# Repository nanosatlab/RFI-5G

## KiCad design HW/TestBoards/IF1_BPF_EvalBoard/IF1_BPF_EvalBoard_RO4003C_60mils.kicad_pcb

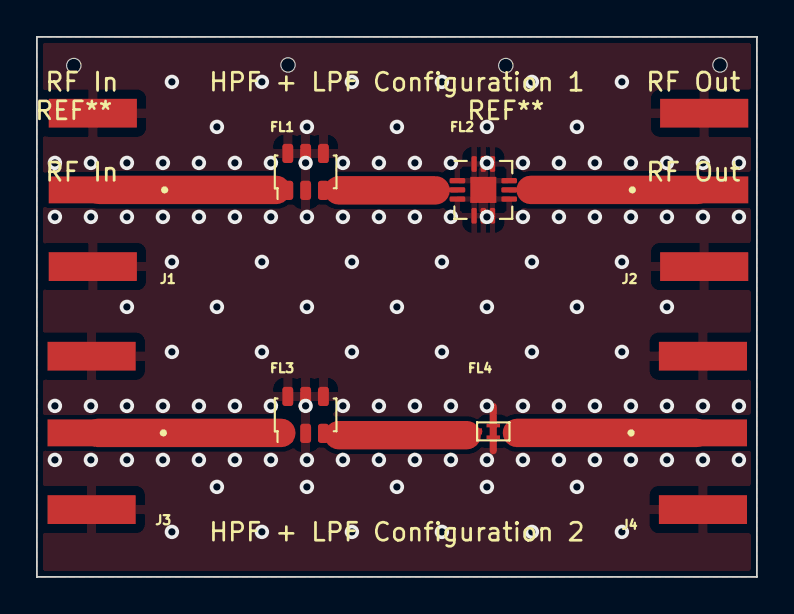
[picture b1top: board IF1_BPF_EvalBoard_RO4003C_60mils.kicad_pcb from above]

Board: 2 copper layers, 40.0 x 30.0 mm, 8 parts (0 on the bottom side), 7 nets.

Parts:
FL1, FL3: HFCN-5500; Filter_Mini-Circuits_FV1206-1
FL2: XLF-962+; QFN-12-1EP_3x3mm_P0.51mm_EP1.45x1.45mm
FL4: LFCW-8000+; JC0603C-1
J1, J2, J3, J4: SMA; LINX_CONSMA020.062-G

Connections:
/HPF_out1: FL1.3 (OUT), FL2.2 (In)
/HPF_out2: FL3.3 (OUT), FL4.1 (In)
/RF_In1: FL1.1 (IN), J1.1 (RF)
/RF_In2: FL3.1 (IN), J3.1 (RF)
/RF_Out1: FL2.8 (Out), J2.1 (RF)
/RF_Out2: FL4.3 (Out), J4.1 (RF)
GND: FL1.2 (GND), FL1.4 (GND), FL1.5 (GND), FL1.6 (GND), FL2.1 (GND), FL2.3 (GND), FL2.4 (NC), FL2.5 (NC), FL2.6 (NC), FL2.7 (GND), FL2.9 (GND), FL2.10 (NC), FL2.11 (NC), FL2.12 (NC), FL2.13 (NC), FL3.2 (GND), FL3.4 (GND), FL3.5 (GND), FL3.6 (GND), FL4.2 (GND), FL4.4 (GND), J1.S1, J1.S2, J1.S3, J1.S4, J2.S1, J2.S2, J2.S3, J2.S4, J3.S1, J3.S2, J3.S3, J3.S4, J4.S1, J4.S2, J4.S3, J4.S4

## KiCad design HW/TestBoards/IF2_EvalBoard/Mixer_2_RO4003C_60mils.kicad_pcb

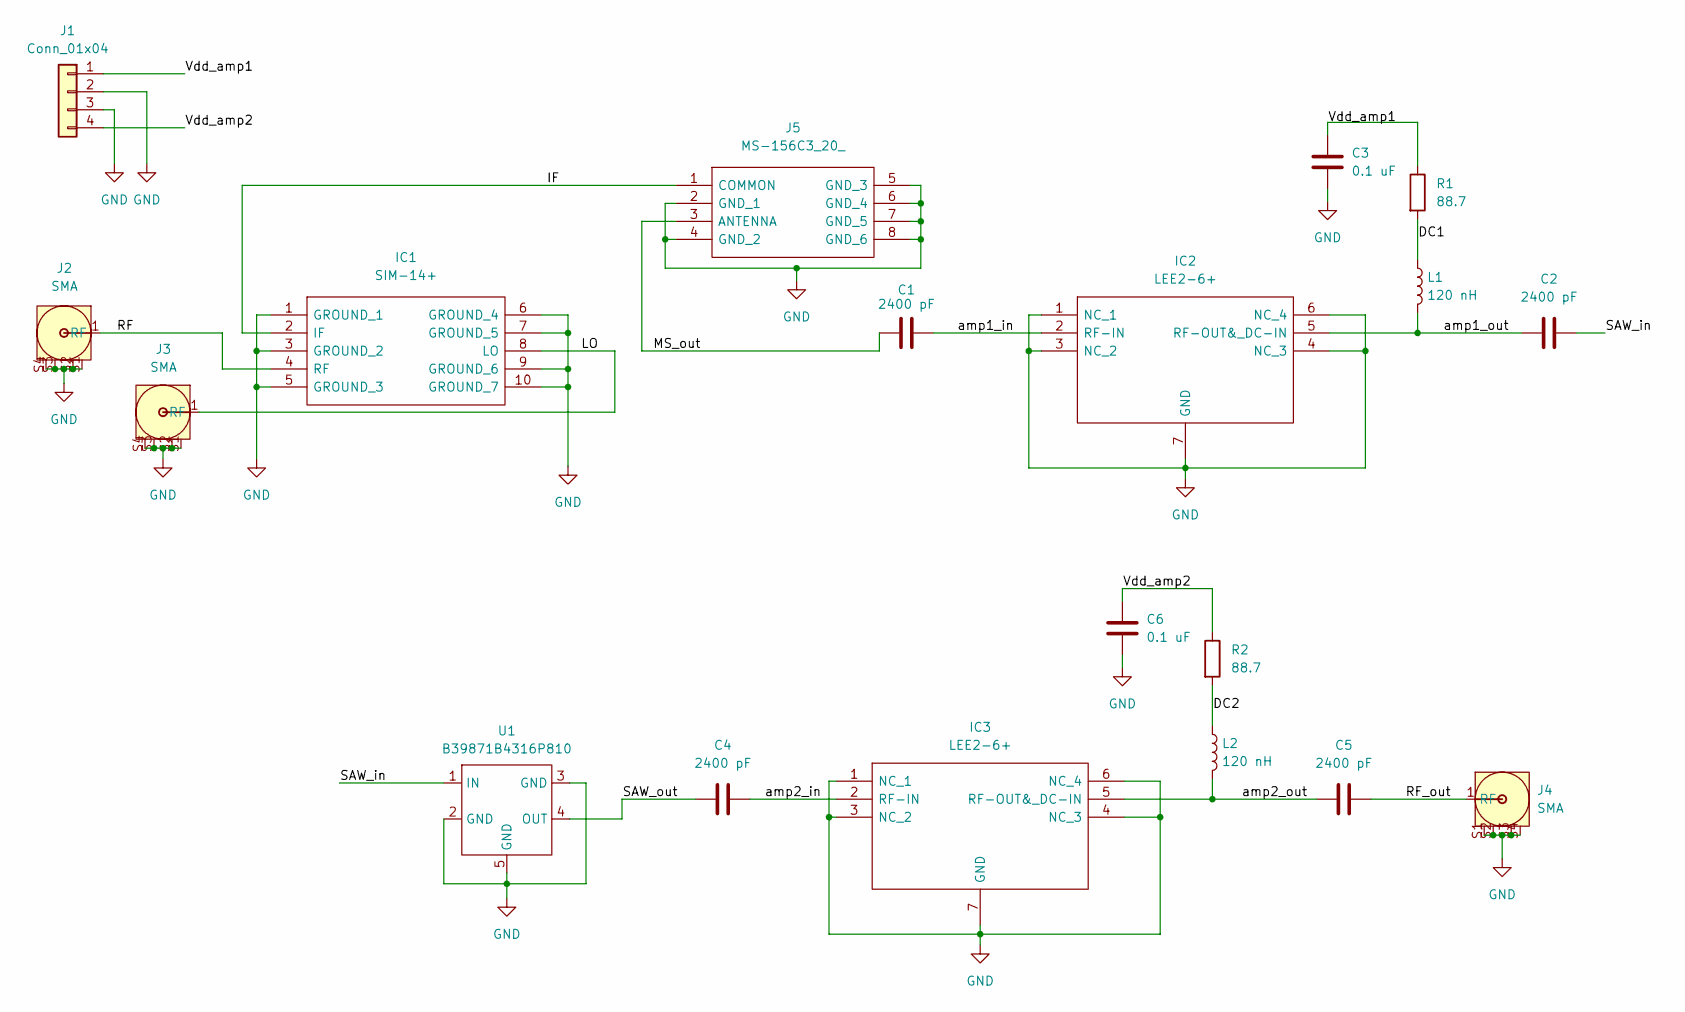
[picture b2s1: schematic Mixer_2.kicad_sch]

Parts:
C1, C2, C4, C5: 2400 pF; C_0603_1608Metric_Pad1.08x0.95mm_HandSolder
C3, C6: 0.1 uF; C_0603_1608Metric_Pad1.08x0.95mm_HandSolder
IC1: SIM-14+; SIM14; Manufacturer_Part_Number SIM-14+
IC2, IC3: LEE2-6+; SON65P200X200X105-7N; Mouser Part Number 139-LEE2-6
J1: Conn_01x04; PinHeader_1x04_P1.27mm_Vertical
J2, J3, J4: SMA; LINX_CONSMA020.062-G
J5: MS-156C3_20_; MS156C320; Mouser Part Number 798-MS-156C320
L1, L2: 120 nH; L_0402_1005Metric_Pad0.77x0.64mm_HandSolder
R1, R2: 88.7; R_0402_1005Metric_Pad0.72x0.64mm_HandSolder
U1: B39871B4316P810

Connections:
/DC1: L1.1, R1.2
/DC2: L2.1, R2.2
/IF: IC1.2 (IF), J5.1 (COMMON)
/LO: IC1.8 (LO), J3.1 (RF)
/MS_out: C1.1, J5.3 (ANTENNA)
/RF: IC1.4 (RF), J2.1 (RF)
/RF_out: C5.2, J4.1 (RF)
/SAW_in: C2.2, U1.1 (IN)
/SAW_out: C4.1, U1.4 (OUT)
/Vdd_amp1: C3.2, J1.1, R1.1
/Vdd_amp2: C6.2, J1.4, R2.1
/amp1_in: C1.2, IC2.2 (RF-IN)
/amp1_out: C2.1, IC2.5 (RF-OUT&_DC-IN), L1.2
/amp2_in: C4.2, IC3.2 (RF-IN)
/amp2_out: C5.1, IC3.5 (RF-OUT&_DC-IN), L2.2
GND: C3.1, C6.1, IC1.1 (GROUND_1), IC1.3 (GROUND_2), IC1.5 (GROUND_3), IC1.6 (GROUND_4), IC1.7 (GROUND_5), IC1.9 (GROUND_6), IC1.10 (GROUND_7), IC2.1 (NC_1), IC2.3 (NC_2), IC2.4 (NC_3), IC2.6 (NC_4), IC2.7 (GND), IC3.1 (NC_1), IC3.3 (NC_2), IC3.4 (NC_3), IC3.6 (NC_4), IC3.7 (GND), J1.2, J1.3, J2.S1, J2.S2, J2.S3, J2.S4, J3.S1, J3.S2, J3.S3, J3.S4, J4.S1, J4.S2, J4.S3, J4.S4, J5.2 (GND_1), J5.4 (GND_2), J5.5 (GND_3), J5.6 (GND_4), J5.7 (GND_5), J5.8 (GND_6), U1.2 (GND), U1.3 (GND), U1.5 (GND)

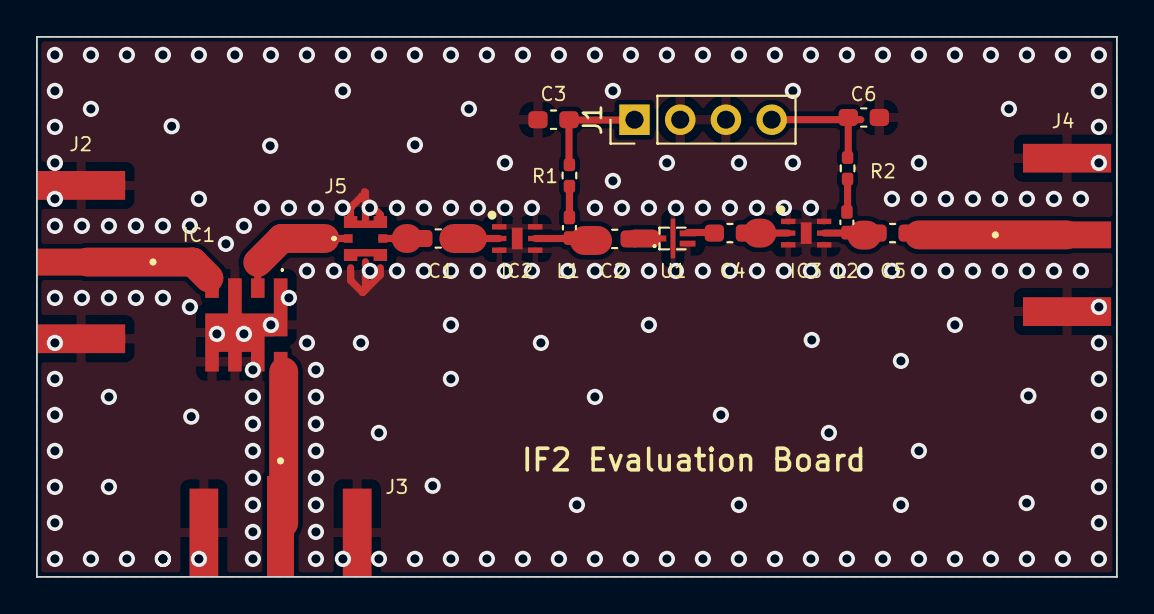
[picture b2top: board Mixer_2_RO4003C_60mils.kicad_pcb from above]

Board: 2 copper layers, 60.0 x 30.0 mm, 19 parts (0 on the bottom side), 16 nets.

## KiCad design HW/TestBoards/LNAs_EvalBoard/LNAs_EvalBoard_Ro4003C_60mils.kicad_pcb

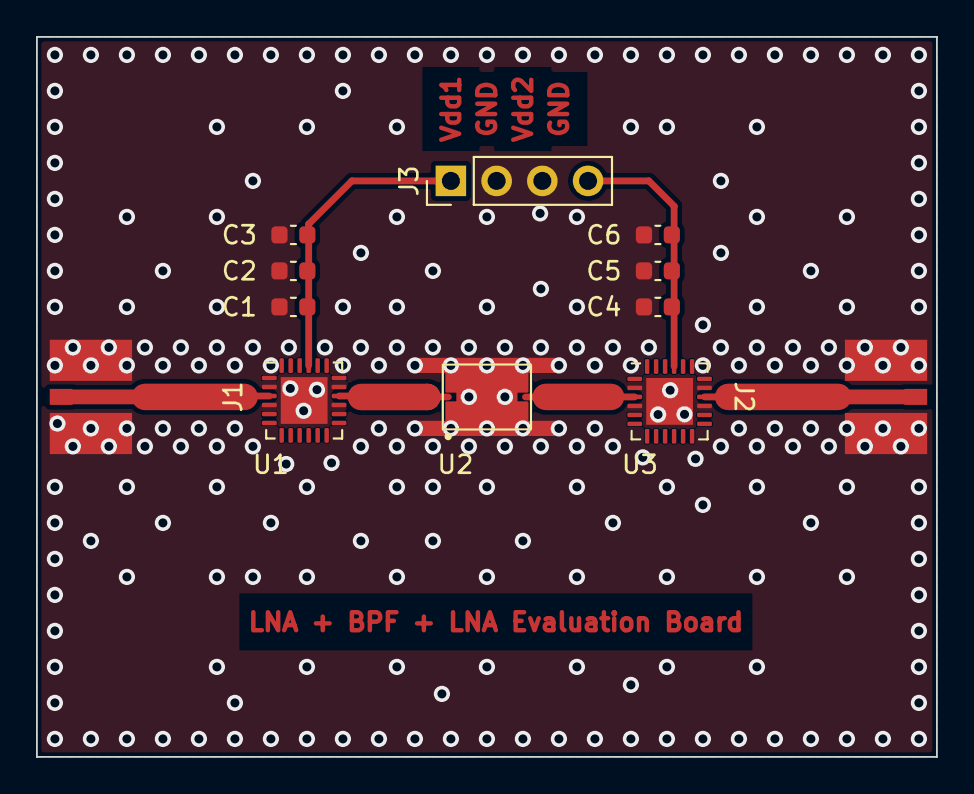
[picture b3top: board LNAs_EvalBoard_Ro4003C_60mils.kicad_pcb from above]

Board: 2 copper layers, 50.0 x 40.0 mm, 12 parts (0 on the bottom side), 6 nets.

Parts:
C1, C4: 100 pF; C_0603_1608Metric
C2, C5: 1 nF; C_0603_1608Metric
C3, C6: 2.2 uF; C_0603_1608Metric
J1, J2: SMA; Johnson_142-0761-861
J3: Conn_01x04; PinHeader_1x04_P2.54mm_Vertical
U1, U3: HMC342; QFN-24-1EP_4x4mm_P0.5mm_EP2.6x2.6mm
U2: BFHK-2582+; NM1812C-2

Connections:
/RF_In: J1.1, U1.3 (RFin)
/RF_Out: J2.1, U3.16 (RFout)
GND: C1.2, C2.2, C3.2, C4.2, C5.2, C6.2, J1.S1, J1.S2, J2.S1, J2.S2, J3.2, J3.3, U1.2 (GND), U1.4 (GND), U1.15 (GND), U1.17 (GND), U1.25 (GND), U2.3 (GND), U3.2 (GND), U3.4 (GND), U3.15 (GND), U3.17 (GND), U3.25 (GND)
unnamed: U1.16 (RFout), U2.1 (IN)
unnamed: U2.2 (Out), U3.3 (RFin)
VDD: C1.1, C2.1, C3.1, C4.1, C5.1, C6.1, J3.1, J3.4, U1.21 (Vdd), U3.21 (Vdd)

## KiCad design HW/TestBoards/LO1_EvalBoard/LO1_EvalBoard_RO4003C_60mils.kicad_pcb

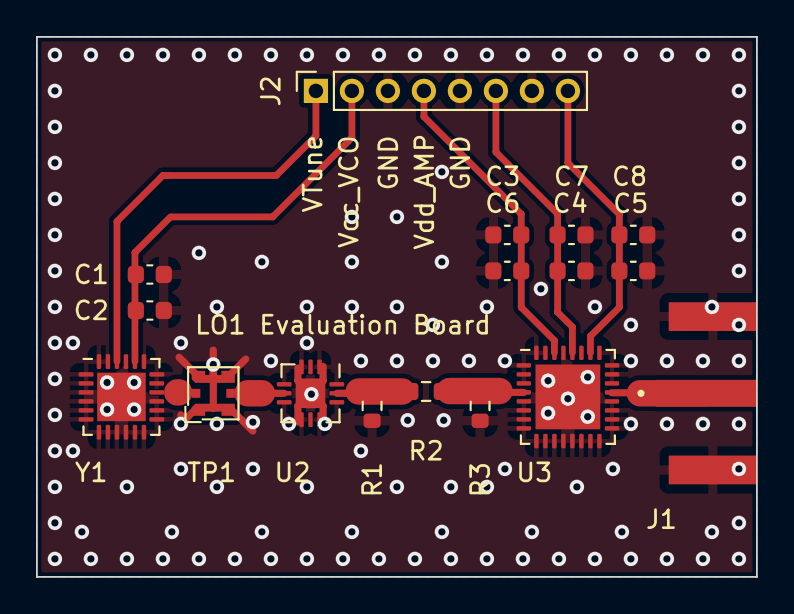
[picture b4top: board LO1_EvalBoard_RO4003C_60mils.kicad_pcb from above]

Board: 2 copper layers, 40.0 x 30.0 mm, 17 parts (0 on the bottom side), 11 nets.

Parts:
C1: 10 nF; C_0603_1608Metric
C2: 4.7 uF; C_0603_1608Metric
C3, C4, C5: 100 pF; C_0603_1608Metric
C6, C7, C8: 2.2 uF; C_0603_1608Metric
J1: SMA; LINX_CONSMA020.062-G
J2: Conn_01x08; PinSocket_1x08_P2.00mm_Vertical
R1, R3: 100 R; R_0603_1608Metric
R2: 50 R; R_0603_1608Metric
TP1: MS-156C; CoaxialSwitch_Hirose_MS-156C3_Horizontal
U2: CY2-44+; QFN-12-1EP_3x3mm_P0.5mm_EP1.65x1.65mm
U3: HMC516; QFN-32-1EP_5x5mm_P0.5mm_EP3.6x3.6mm
Y1: HMC506LP4; QFN-24-1EP_4x4mm_P0.5mm_EP2.7x2.7mm

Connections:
/Att_out: R2.2, R3.2, U3.4 (In)
/FD_out: R1.1, R2.1, U2.11 (Out)
/RFOut: J1.1 (RF), U3.21 (Out)
/TP_out: TP1.A (Out), U2.5 (In)
/VCO_out: TP1.C (In), Y1.16 (RFout)
/VTune: J2.1, Y1.22 (VTune)
/Vcc_VCO: C1.1, C2.1, J2.2, Y1.20 (Vcc)
/Vdd_Amp1: C3.1, C6.1, J2.4, U3.30 (Vdd1)
/Vdd_Amp2: C4.1, C7.1, J2.6, U3.28 (Vdd2)
/Vdd_Amp3: C5.1, C8.1, J2.8, U3.26 (Vdd3)
GND: C1.2, C2.2, C3.2, C4.2, C5.2, C6.2, C7.2, C8.2, J1.S1, J1.S2, J1.S3, J1.S4, J2.3, J2.5, J2.7, R1.2, R3.1, TP1.G (GND), U2.1 (GND), U2.3 (GND), U2.4 (GND), U2.6 (GND), U2.7 (GND), U2.9 (GND), U2.10 (GND), U2.12 (GND), U2.13 (GND), U3.1 (NC), U3.2 (NC), U3.3 (GND), U3.5 (GND), U3.6 (NC), U3.7 (NC), U3.8 (NC), U3.9 (NC), U3.10 (NC), U3.11 (NC), U3.12 (NC), U3.13 (NC), U3.14 (NC), U3.15 (NC), U3.16 (NC), U3.17 (NC), U3.18 (NC), U3.19 (NC), U3.20 (GND), U3.22 (GND), U3.23 (NC), U3.24 (NC), U3.25 (GND), U3.27 (GND), U3.29 (GND), U3.31 (GND), U3.32 (NC), U3.33 (GND), Y1.1, Y1.2, Y1.3, Y1.4, Y1.5, Y1.6, Y1.7, Y1.8, Y1.9, Y1.10, Y1.11, Y1.12, Y1.13, Y1.14, Y1.15 (GND), Y1.17, Y1.18, Y1.19, Y1.21, Y1.23, Y1.24, Y1.25 (GND)

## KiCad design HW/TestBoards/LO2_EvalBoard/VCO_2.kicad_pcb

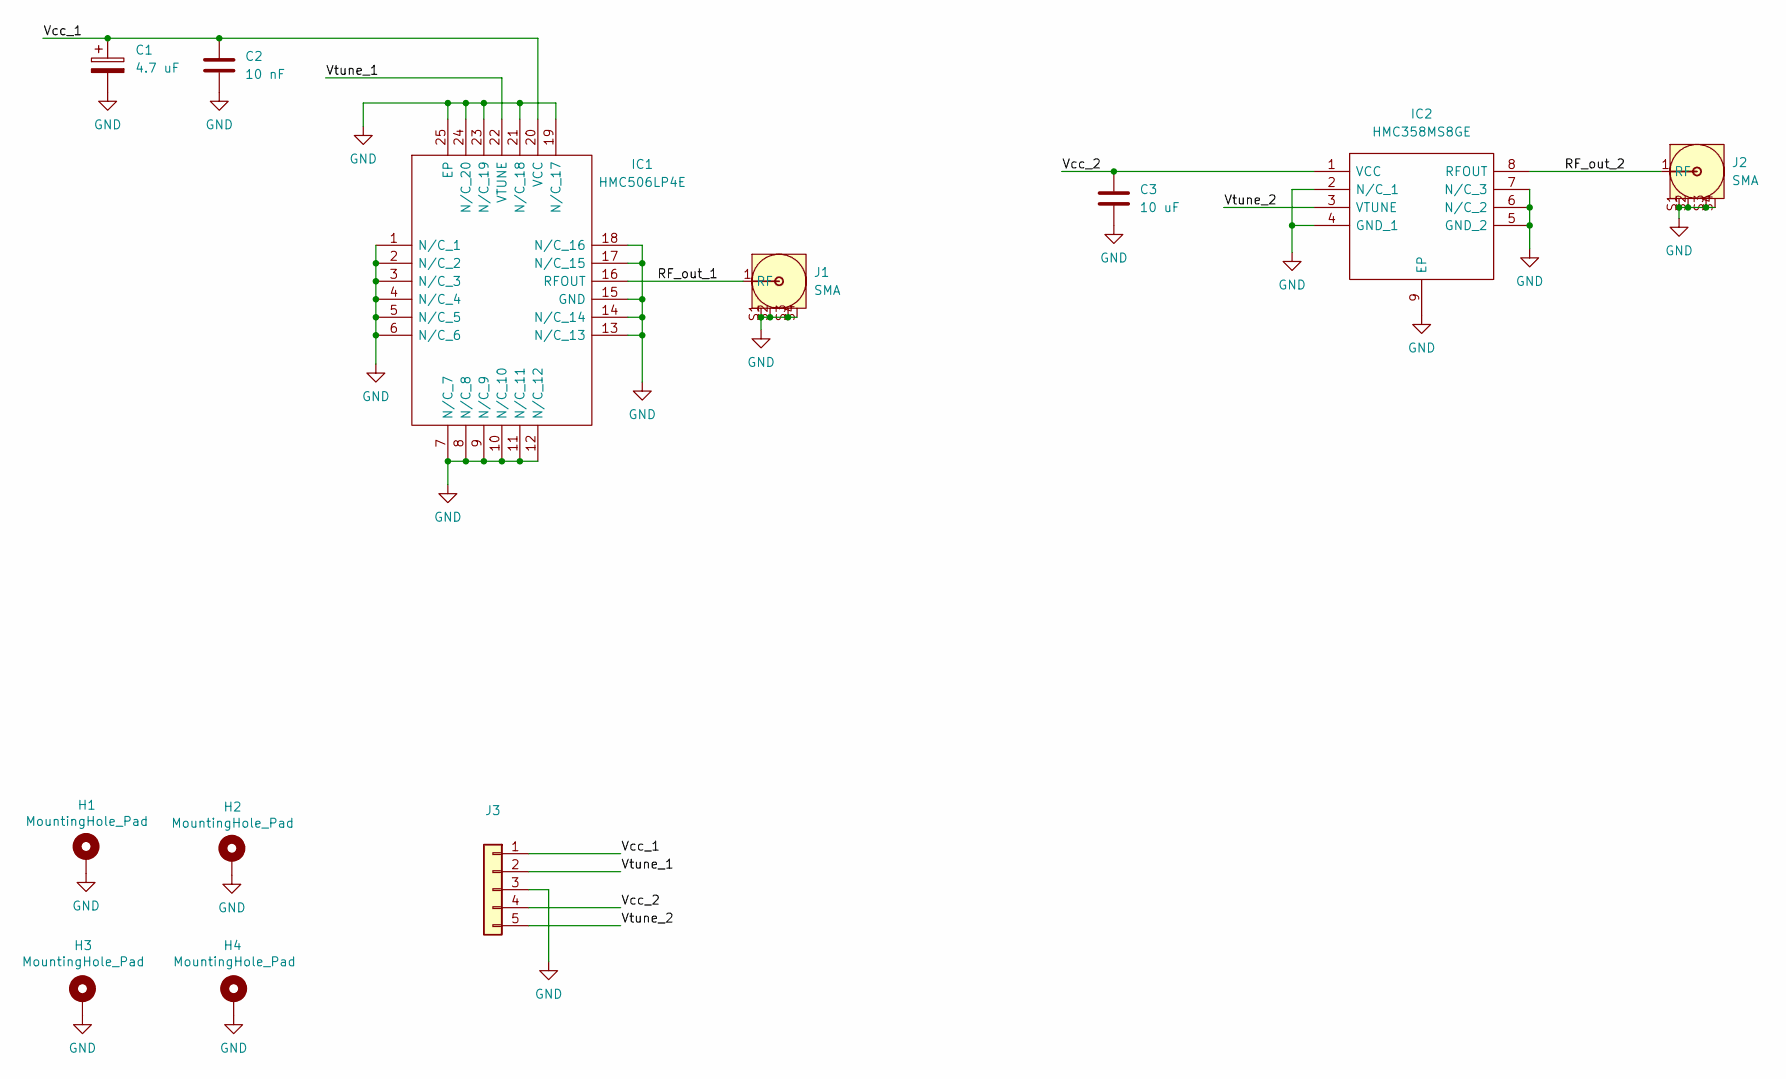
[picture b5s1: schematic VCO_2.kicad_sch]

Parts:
C1: 4.7 uF; C_0603_1608Metric_Pad1.08x0.95mm_HandSolder
C2: 10 nF; C_0603_1608Metric_Pad1.08x0.95mm_HandSolder
C3: 10 uF; C_0603_1608Metric_Pad1.08x0.95mm_HandSolder
H1, H2, H3, H4: MountingHole_Pad; MountingHole_2.5mm_Pad
IC1: HMC506LP4E; QFN50P400X400X100-25N; Mouser Part Number 584-HMC506LP4E
IC2: HMC358MS8GE; SOP65P488X110-9N; Mouser Part Number 584-HMC358MS8GE
J1, J2: SMA; LINX_CONSMA020.062-G
J3: (no value)

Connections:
/RF_out_1: IC1.16 (RFOUT), J1.1 (RF)
/RF_out_2: IC2.8 (RFOUT), J2.1 (RF)
/Vcc_1: C1.1, C2.1, IC1.20 (VCC), J3.1
/Vcc_2: C3.1, IC2.1 (VCC), J3.4
/Vtune_1: IC1.22 (VTUNE), J3.2
/Vtune_2: IC2.3 (VTUNE), J3.5
GND: C1.2, C2.2, C3.2, H1.1, H2.1, H3.1, H4.1, IC1.1 (N/C_1), IC1.2 (N/C_2), IC1.3 (N/C_3), IC1.4 (N/C_4), IC1.5 (N/C_5), IC1.6 (N/C_6), IC1.7 (N/C_7), IC1.8 (N/C_8), IC1.9 (N/C_9), IC1.10 (N/C_10), IC1.11 (N/C_11), IC1.12 (N/C_12), IC1.13 (N/C_13), IC1.14 (N/C_14), IC1.15 (GND), IC1.17 (N/C_15), IC1.18 (N/C_16), IC1.19 (N/C_17), IC1.21 (N/C_18), IC1.23 (N/C_19), IC1.24 (N/C_20), IC1.25 (EP), IC2.2 (N/C_1), IC2.4 (GND_1), IC2.5 (GND_2), IC2.6 (N/C_2), IC2.7 (N/C_3), IC2.9 (EP), J1.S1, J1.S2, J1.S3, J1.S4, J2.S1, J2.S2, J2.S3, J2.S4, J3.3

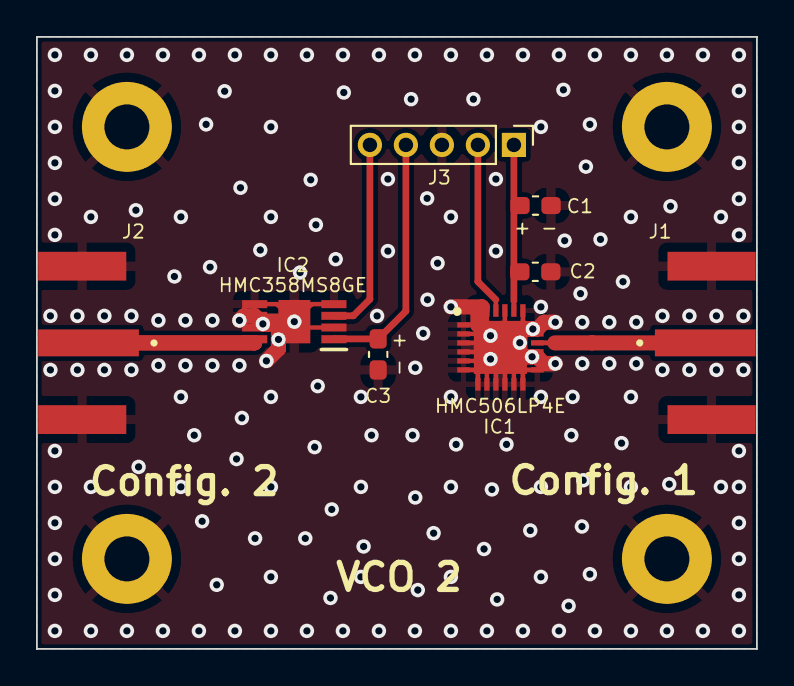
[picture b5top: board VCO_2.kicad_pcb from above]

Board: 2 copper layers, 40.0 x 34.0 mm, 12 parts (0 on the bottom side), 7 nets.
